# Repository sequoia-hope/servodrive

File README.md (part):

# servodrive

A round, motor-mounted servodrive: two Ø65 mm boards stacked on the back of a
brushless motor, with a magnetic rotary encoder on the shaft axis.

**Status: board A captured, placed and routed. 136 parts, 87 nets,
425 pin connections, every one of them made. DRC- and ERC-clean, and
KiCad's own extracted netlist matches the intended one connection for
connection. Re-routed 2026-09-22 with four of the simulation's changes
([below](#the-2026-09-22-changes)); board B is still an outline.
Board S, the single-board variant, captured, placed and routed 2026-09-23
from the same generators, re-routed the same day with TI's buck parts, and
re-placed and re-routed 2026-09-24 with an XT30 for the bus
([below](#board-s-one-board)).**

- **[spec.html](spec.html)** — the specification
- **[index.html](index.html)** — status, decisions, open questions; board A in the viewer (PCB and 3D tabs)
- **[single.html](single.html)** — board S, the single-board variant: captured, placed and routed, with the same viewer (SCH, PCB and 3D)

The pages are styled after Altium 365's workspace: a dark frame with the
project tree on the left, built by `shell.js` from each page's own headings.
The board viewer on the two board pages is
[pcbview](https://github.com/sequoia-hope/pcbview)'s (which began as this
project's own; `tools/regen.py` runs it from `~/Software/pcbview`):
`pcbview.toml` says what it shows, and `python3 tools/regen.py --board a|s`
builds it into `viewer/` and writes it into the page between
`<!-- pcbview:begin -->` and `<!-- pcbview:end -->`.
`viewer/a.html` and `viewer/s.html` are the same viewers filling the window.

Online at <https://sequoia-hope.github.io/servodrive/> (GitHub Pages, from
the root of `main`: the pages are plain files with relative links, and
`.nojekyll` keeps them that way). Served locally: `proj up servodrive`, then
`proj url servodrive` for the address.

## What it is

| | |
|---|---|
| Form | Two Ø65 mm round boards. The motor board bolts to the encoder's 4 × M3 pattern; the power/IO board to six perimeter M2.5. |
| Sections | Three 60° phase cells **adjacent**, 0–180°, then three 60° wedges. The CPU sits in the middle wedge, as far from the switching as a round board allows. |
| Encoder | MT6701 on the shaft axis, SSI to the CPU on the same board. No cable, no line drivers, no encoder port. |
| Bus | 60 V nominal, **12 V minimum**, 80 V silicon, TVS breakdown 71–79 V; XT30 |
| Phase current | **20 A RMS per phase, in bursts** — normal running is well below it, and no fins are planned (§4) |
| CPU | RP2350A, QFN-60 |
| Sensing | Two inline 1.0 mΩ shunts (2 × 2 mΩ) + **INA241A3** at 50 V/V = 50 mV/A, third phase reconstructed; bus voltage; FET temperature |
| Gate drive | EG2103 on a 12 V rail (LCSC C480654, 2,225 in stock, MOQ 5, $0.19) — interlock + 560 ns dead time |
| I/O | USB-C with full PD — a 20 V contract feeds VMOT; full-duplex RS-485 on two chained ports |

## The design point is 20 A RMS, and that word matters

Draft 0.2 used "20 A" for two different quantities: the thermal budget quoted
20 A **RMS per phase**, and the sense chain quoted ±20.6 A **instantaneous**.
Those differ by √2, so the sense chain clipped at 14.6 A RMS — it could not have
closed a current loop at the design point. One number now, and everything is
sized against it:

| | |
|---|---|
| Design point | 20 A RMS per phase — a burst figure since 2026-09-22, not a continuous rating |
| Peak the chain must see | 28.3 A |
| Sense full scale | ±29.0 A, worst-case output swing — 2.5% over the peak, see below |
| Board A dissipation | 10.7 W |
| Heatsink it would need to be continuous | ≤ 6.7 K/W, ≥ 100 cm² of external surface — not built |

## Current sensing

Full scale is set by the shunt. Keep this table, the schematic and the firmware
`SHUNT_RESISTOR` define pointed at each other — the sister project's F-14 is
exactly this drifting apart.

| Shunt (per sensed phase) | Gain | V/A | Measurable range |
|---|---|---|---|
| 1.0 mΩ (2 × 2 mΩ 2010) | 50 V/V | 0.050 | ±29.0 A |
| 2 mΩ (one desoldered) | 50 V/V | 0.100 | ±14.5 A |

Phase C is reconstructed as `Ic = -(Ia + Ib)`. Its two shunt footprints are
fitted with 0 Ω links so all three phases have the same series resistance.

Full scale is against the datasheet's **worst-case** output swing, V<sub>S</sub> − 0.2 V,
not the 0.07 V typical — that is what makes ±29.0 A rather than ±32 A, and it is
the number the design point has to clear. It does, by 2.5%.

**This took three goes.** Draft 0.2's 1.6 mΩ gave 80 mV/A to match the sister
project's firmware scaling, and ±20.6 A of full scale against a 28.3 A peak: it
would have clipped on every cycle above 14.6 A RMS. The first correction, 1.0 mΩ,
used the typical swing figure and had 2.5% of margin, which is not margin. 0.8 mΩ
(2 × 1.6 mΩ) survived the datasheet, and its precision mode landed on the sister
project's 80 mV/A. Then sourcing (2026-09-24) found no 1.6 mΩ 2010 at LCSC or
JLCPCB — 1 and 2 mΩ, nothing between — and the pair became 2 × 2 mΩ: back at
1.0 mΩ and its 2.5%, taken knowingly. The stocked alternative, 2 × 1 mΩ, reads
±58 A at 25 mV/A. Neither mode reproduces the sister project's 80 mV/A now, so
its firmware constants do not carry across.

**And the part number changed.** The 50 V/V grade of INA241 is **A3**, not A2.
INA240 numbers its gains A1 = 20, A2 = 50; INA241 numbers them A1 = 10, A2 = 20,
A3 = 50. Draft 0.2 carried the INA240 mapping across and specified a 20 V/V part
for a 50 V/V job.

## Relationship to rp2350-motor-controller

The sister project at `~/pcb/rp2350-motor-controller` supplies the MT6701
encoder circuit and its mount pattern (`hardware/encoder`), the power-stage part
choices, and a findings register that this board inherits the conclusions of
without inheriting the bugs. §9 of the spec lists which finding produced which
decision here.

Three things worth handing back:

- **F-17 is right, and draft 0.2 of this spec was wrong to doubt it — but not
  for the reason their register gives.** Their E-stop does brake. It brakes
  because `R1`, `R2`, `R21` and `R22` are 10 k pull-downs on both EG3113 inputs,
  and EG3113's LIN is active-low: a pulled-down LIN turns the low-side FET on.
  The driver on its own would coast. The consequence is worth knowing: their
  bridge **hard-shorts the motor at every reset and every power-up**, before
  firmware runs, with no current limit. On a spinning motor that is a braking
  current set only by winding resistance.
- **NCP5183DR2G** is a candidate answer to **F-40** (EG3113 unbuyable, currently
  blocking their orders): SOIC-8, 600 V, 4.3 A source/sink, matched 120 ns
  propagation delays, 50 V/ns dV/dt immunity, AEC-Q100, $0.92 at MOQ 1 with 2,883
  in stock. It gives up EG3113's interlock and dead time, which their own GaN
  evaluation argues they do not lean on. Also worth knowing: **EG2131 and FD2103S,
  the two obvious like-for-like swaps, are both out of stock.**
- **RP2350 erratum E9 reaches the gate driver.** A Bank 0 GPIO can latch around
  2.1–2.2 V, and at reset the pin is an input with a pull-down. Against EG Micro's
  internal 200 k pull-up on LIN that lands the driver input between V<sub>IL</sub>
  and V<sub>IH</sub>. Their pull-downs happen to defeat it; anyone copying the
  circuit without them should size an external pull deliberately.

## The channel interior to the screws

A phase cell is short of **angle**, not of area, and angle costs radius: a
millimetre of arc at R 20 is 2.9°, the same millimetre at R 29.5 is 1.9°. The
cell was 70° wide because small parts sat at small radius — a 1 µF 0805 beside
the gate driver was eating 30° on its own, while both MOSFETs together needed
only 18°.

The six boss pads sit on R 26.9–32.2, and **between them that band is empty**:
the heatsink land owns it on the outward face, and on the motor-facing face
nothing but the lead pads wants it. In the utility wedges that is still true and
the channel is still used. In a **phase** cell it turned out not to be — see
below — and only the clamp diode is left there, beside its own lead pad.

| | 70° cells | everything in the channel | **now** |
|---|---|---|---|
| Phase cell | 70° | 60° | **68°** |
| Utility wedge | 50° | 60° | **52°** |
| Bolt spacing | 70/70/70/50/50/50° | 60°, even | **68/68/68/52/52/52°** |
| In the channel, per cell | — | 6 parts | **1** — the clamp diode |
| Heatsink land | 286 mm² | 250 mm² | **279 mm²** |

**Routing took most of that back, and it was right to.** The middle column is
what the channel bought: 60° cells and an even bolt circle. What it cost only
showed up when the board was routed — a part in the channel can only be
connected if its nets are GND or the phase output, because the phase-output
pour owns B.Cu from R 25.9 to 28.9 beneath it, the heatsink land owns F.Cu from
R 29.2 above it, and the six boss pads cut the outer ring into six arcs. What
is left is a via corridor about 0.7 mm wide, twice per cell. Neither pour can
give the room back: the phase band is already 95 A/mm² at 3.0 mm and cannot
grow inward past R 25.6 without meeting the switch-node band.

So five of the six went back into the cell — the DC-link 100 n pair into the
DC-link row *ahead* of the bulk, where a high-frequency capacitor belongs; the
bootstrap diode beside the capacitor it charges; both input pulls onto the
driver's logic side with the VCC 100 n. Only the clamp diode stays, and its
nets are exactly GND and the phase output.

The cells had to pay for them: 67° is the floor, below which the DC-link row
runs into the perimeter boss, and 68° is what is set. That costs the even bolt
circle — the thing the 60° arrangement was pleasing for. It buys back
**29 mm² of heatsink land**, because the land's half-span is measured from the
cell edge.

Three consolidations paid for it: the per-driver 1 µF VCC bulk became one 4.7 µF
at the power link (three of them on one 0.1 A rail was two too many), the lead
pad narrowed from ±8.5° to ±7° (23 mm², still ample for a 14 AWG lead), and
`Row` learned to dodge parts in *other* rows — two rows that overlap radially
and sit at different angles can collide, and a packer that only looks at its own
row walks straight into them.

## The layout, second pass

The first routed board made 69 of 170 connections, and the diagnosis at
the time blamed the driver ring. Measuring the result said otherwise:
nearly every unrouted connection ended at the RP2350. In3, the only signal
layer that crosses the board, was almost empty, because nothing could get
out of the QFN to reach it. Three things were true of that board and are
not of this one.

**The QFN had no room to fan out.** A 0.4 mm pitch, 0.2 mm-wide pads, and a
via that is 0.46 mm across with 0.15 mm around it: a via per pin does not
fit in place, and it does not fit in two rows either. With 0.15 mm stubs it
takes four staggered rows, 2.9 mm deep, on every side — and the chip sat
0.3 mm from the parts either side of it, 0.8 mm from the row beyond it,
with its decoupling on the back directly under the pins where the vias had
to land. The CPU wedge is rebuilt around a clear band: the chip at R 21.15,
nothing within 2.9 mm of its pads on the front except the regulator
cluster (below), the six IOVDD 100 n on the back in two columns beside it,
the crystal in a row at R 29.9, and the flash turned so both its pad rows
face somewhere a via can go, with its own 100 n and the BOOTSEL resistor on
the back directly beneath its body. The signal header moved in to R 25.15,
where all twenty of its signal pads can take an escape via on the side away
from the edge.

**The FET gate pads faced the wrong way.** The gate is at one end of the
TDSON-8's source-pad row, and with the row pointing outward the gate sat at
R 27.9, walled in by the switch-node pour on three sides and the heatsink
land on the fourth. Both FETs are turned 180°, which swaps their sides, and
the gate pads are at R 24.4 facing the driver row across an empty 1.5 mm.
The gate resistors and input pulls are 0402s lying tangentially, so HO and
LO reach a pad at their own radius and the far pad points at the gate; the
bootstrap cap is a 0603 with its SW pad over the switch-node pour, so it
takes a via.

**The sense row on the back is arranged for arcs, not for a router.** The
amplifier is at the cell's centre with its SNSP pin, the switch-node-side
tap and the filter cap all clockwise of it within 0.4 mm of R 18.4, so
that SNSP is one arc between the amplifier's pad rows with a spur down to
each pad, and SNSN is a second arc beside it to the filter cap, a via at
the amplifier and a via in the tap at the shunt, and one run on In3
between them. The gate bleeds moved from that row to directly beneath the
gate resistors: the high side's radial under its resistor, the low side's
further out under the gate's own radial track, each with one via through
both pads. The NTC moved inside the row where its pad can take a via. The
flash is turned so that each pad row's radial order is the chip's QSPI pin
order along its side and the In3 runs between them do not cross.

**Every 20 A pad takes a via, and the router never sees those nets.** The
shunts moved from either side of the cell to side by side under the
switch-node island, between the two FETs' via clusters — nowhere else on
the back is clear of the DC-link caps' vias coming through from the other
face — with the SW pads over the switch-node pour and the PHASE pads in the
phase-output pour, the lead pad directly beyond. The sense taps sit beside
them, the clamp in the channel beside the lead pad where the pour reaches
out to it. The switch-node pour on B.Cu comes in to R 20 so the driver's VS
pin, the bootstrap cap, the bleed and the tap all stitch. +3V3 is a plane on
In2 that is now the whole centre disc as well as the CPU wedge, so each
cell's sense amplifier taps it with a stub. With all of that
stitched, `tools/deadcheck.py` proves it and `route.py` takes VBUS, the
switch nodes, the phase outputs and +3V3 away from the router: pours become
keepouts, pads lose their net and get a halo the width of their clearance
class. It cost the cells 0.9 mm of FET spacing, a 1206 DC-link bulk cap
instead of a 1210 (the 1210 ran into the perimeter boss), and a SOD-323
bootstrap diode.

### The RP2350, from the reference design

The chip's regulator and decoupling are Raspberry Pi's, copied from the
RP2350A minimal design (RP-006440) in the chip's own frame to the 0.05 mm:
the 3.3 µH 2016 inductor 3.8 mm from VREG_LX with the VIN, DVDD and AVDD
4.7 µF stacked beside it, the two by the inductor on the reference's own
small-pad 0402 footprint because the switch node's neck passes between
their pads; 33 Ω into VREG_AVDD; 27 Ω in series with each USB line; five
small pours around the regulator pins; a ring of 1V1 copper under the chip
joining the four DVDD pins, which the fan-out tool reaches with a stub from
each; and the reference's own two F.Cu tracks, VREG_AVDD out to its RC and
DVDD pin 50 out to the regulator's output pour (the second is only laid if
the fan-out beside it leaves the room, and here it does not, so the ring
and the output pour meet through a via each and a run on In3 that the
fan-out tool lays itself, dodging the via field). Two of the pours turned
out not to fill under the 0.15 mm clearance this board runs — between two
0.4 mm-pitch pads a pour is 0.3 mm wide and breaks at their corners — so
VREG_LX gets a 0.15 mm track as well, threaded between the VIN capacitor's
pads the way the reference's pour is.

Three things capture found while doing it, all in the netlist rather than
the layout:

- **The bootstrap diode was backwards.** `Device:D` numbers its pins
  1 = cathode, 2 = anode, and so does the footprint; the netlist had the
  cathode on +12V. A bootstrap diode charges the cap *from* the rail.
- **VREG_AVDD was tied straight to +3V3.** The reference feeds it through
  33 Ω with its own 4.7 µF.
- **USB had no series resistors.** 27 Ω each, as the reference.

The crystal's load caps stay at 27 p where the reference uses 15 p: the
reference's crystal is a different part with a different CL, and the value
is the crystal's to decide.

## Layout

```
tools/sexp.py        a reader/writer for KiCad's s-expressions
tools/geometry.py    every dimension and every derived number; regenerates img/*.svg
tools/placement.py   the board-A floorplan, and the checks that keep it legal
tools/placement_s.py board S, the single-board variant: its floorplan (layout()),
                     drawn to img/board_s_*.svg and single.html's tables
tools/placement_e.py board E, the Ethernet daughter board: a placement sketch
                     over board S as routed, drawn to img/board_e_plan.svg
tools/schematic.py   the board-A netlist, and the sheets it emits
tools/schematic_s.py board S's netlist, built from schematic.py's own functions
tools/gen_boards.py  emits the KiCad projects from the three above; --board s
                     emits board S alone
tools/stitch.py      puts a via in every pad that sits over its own plane
tools/fanout.py      the copper the router could not make: the RP2350's escape
                     vias, the gate and sense arcs, the escapes, the plane taps
tools/deadcheck.py   proves every pad on a net route.py demotes already
                     touches copper of its own net
tools/padpos.py      pad centres of a placed Part, polar, without a board
tools/finish.py      a maze router over the board's free space, for whatever
                     freerouting gives back still in pieces
tools/route.py       hands the rest to freerouting, headless, and brings it back
tools/regen.py       remakes what the pages show after gen_boards.py or
                     route.py (both run it): the board viewer (pcbview build),
                     board S's build status, board S's simulation
pcbview.toml         the board viewer: which boards and pages, the sheet names,
                     the layer notes, the stand-in 3D models, the LCSC table
hardware/
  parts/3dmodels/    two STEP models the footprints name and KiCad's library
                     lacks, and one it has but kicad-cli cannot mesh, flattened;
                     stand-ins for the 3D viewer, mapped in pcbview.toml
                     (sources in its README)
  parts/lcsc.csv     the LCSC numbers chosen so far, by value and footprint, for
                     the 3D viewer's part pane; a part not in it has none yet
  parts/             two symbols copied in, three DERIVED (EG2103, INA241A3,
                     W25Q16JV; board S's SIT3088, SIT65HVD75 and W25Q80DV too), two copied from the RP2350A reference design
                     (the 2016 inductor, a small-pad 0402) and five GENERATED
                     footprints (the FET with 16 thermal vias for the low side
                     and 20 for the high, heatsink boss, heatsink land, phase pad)
  motor_board/       servodrive_A — 6 layer, 2 oz outer, 136 parts, 87 nets
  power_board/       servodrive_B — 4 layer, 2 oz outer, outline only
  single_board/      servodrive_S — board S, 6 layer, board A plus board B's minimum
img/                 generated drawings — do not edit by hand
viewer/              built by pcbview — do not edit by hand: a/ and s/ (sch/,
                     layers/, 3d/ with board.glb and parts.json), assets/ (its
                     scripts, viewer.css, three.js), a.html and s.html
shell.js             the frame every page shares, after Altium 365: top bar, the
                     PROJECT tree read off each page's headings, the sheet bar
style.css            the one stylesheet, A365's palette (sim/report uses it too);
                     the viewer's own is viewer/assets/viewer.css
vendor/fonts/        Inter, latin and greek (OFL)
spec.html            the specification
index.html           project status
```

The three tools are checked against each other before anything is written:
`gen_boards.py` will not emit a board if the floorplan overlaps itself, or if
any part is on the board and not in the netlist, or in the netlist and not on
the board, or if their footprints disagree, or if a symbol pin has no net.

Run `python3 tools/geometry.py` after changing any dimension, then
`python3 tools/gen_boards.py --force` to re-emit the boards. `gen_boards.py`
refuses to run at all if `placement.py`'s checks fail, so a board that overlaps
itself cannot be written.

`--force` rewrites the boards from scratch, which now means **throwing away the
routing**. Without it `gen_boards.py` keeps the existing `.kicad_pcb` and only
re-renders. `--force` also runs the stitcher and the fan-out, so the board it
writes is already half made; after it, re-run `python3 tools/route.py --rounds 4
--loose` for the rest. The moment you move a part or a track in KiCad by hand,
stop using `--force` at all.

## Hardware

Both projects are KiCad 9, DRC- and ERC-clean. Board origin is the shaft axis on
both, so the stack aligns.

| | Board A | Board B |
|---|---|---|
| Stackup | 6 layer, 2 oz outer / 1 oz inner | 4 layer, 2 oz outer |
| Diameter | Ø65 mm | Ø65 mm |
| Motor mount | 4 × M3 at (±12.5, 0), (0, ±9.5) | — |
| Stack mount | 6 × M2.5 at R = 29.5 | 6 × M2.5 at R = 29.5 |
| Placed | 136 parts, 78 front / 58 back, 10 DNP | — |
| Captured | 136 components, 87 nets, 425 connections | — |
| Routed | 1361 track segments, 278 vias, all 425 connections, **DRC clean** | — |

The F.Cu → In1 prepreg is **0.1 mm**, and that is a load-bearing number, not a
stackup detail: it is what puts the ground plane under the commutation loop and
holds loop inductance at 0.39 nH of PCB, 2.0 nH all in, 1.7 V of overshoot on
80 V silicon.

Design rules: 0.15 mm track and clearance everywhere except the 60 V nets, which
get 0.4 mm; vias 0.5/0.20 signal, 0.6/0.30 power, 0.8/0.40 phase; **0.5 mm
hole-to-hole**. That last one is deliberate — JLCPCB fills and copper-caps
via-in-pad for free on 6-layer boards, which is what lets the pad centres be
holes at all, but it wants 0.5 mm between them, and the sister project's F-48 is
the cost of discovering that after 253 via pairs were already too close.

Two of those numbers moved during routing, and both were wrong before:

- **0.15 mm, not 0.20, on the power and analog classes.** A 0.65 mm-pitch
  VSSOP-8 has 0.15 mm between adjacent pins, so a 0.20 mm class made every
  INA241 a clearance violation that no layout could fix. 0.15 is also JLCPCB's
  floor for 2 oz outer copper, so nothing is given up.
- **0.20 mm drills on the 0.5 mm vias, not 0.25.** The annular ring is
  (diameter − drill) / 2, so 0.25 left 0.125 mm against this project's own
  0.13 mm minimum. The default via was illegal under the default rules, and
  nothing noticed until there were vias on the board to check.

Verify after any change:

```sh
python3 tools/placement.py       # floorplan: overlaps, bounds, cross-layer
python3 tools/schematic.py       # netlist, and that it matches the placement
python3 tools/deadcheck.py hardware/motor_board/servodrive_A.kicad_pcb
python3 tools/route.py --rounds 4 --loose   # route headless, import, finish, DRC
cd hardware
kicad-cli pcb drc motor_board/servodrive_A.kicad_pcb
kicad-cli sch erc motor_board/servodrive_A.kicad_sch
kicad-cli sch export netlist --format kicadsexpr -o /tmp/n.net \
    motor_board/servodrive_A.kicad_sch     # then diff it against schematic.nets()
```

That last one is the check worth keeping: KiCad's own extracted netlist against
the one this repo intended, net by net and connection by connection. It is how
the sub-symbol naming bug below was caught, and it is the only thing that proves
the labels actually connect what they look like they connect.

## Routing

Most of board A is not routed and never will be. GND is two solid inner
planes, VBUS is a sector of a third, +3V3 is the rest of that third — the
CPU wedge and the whole centre disc — and each switch node and phase output
is a pour on F.Cu and B.Cu, because 20 A does not go down a track and
IPC-2152 wants about 6 mm of 2 oz copper for it. What is left is the
signals, and those go to freerouting — less the ones it turned out to do
badly, which are made first, as copper, and taken away from it.

Five tools do the rest, and freerouting is the fourth of them rather than
the whole story. They all run from `gen_boards.py` and `route.py`, so the
board is still reproducible from `geometry.py`:

- `tools/stitch.py` puts a via in every pad that sits over a plane or pour
  of its own net. 104 of them.
- `tools/fanout.py` makes the connections the router could not. It escapes
  the RP2350: a 0.15 mm stub from the centre of every one of its sixty
  pads and a via at the end of it, in planned staggered rows, the stub
  threaded through the rows in front of it. It joins the four DVDD pins to
  the 1V1 ring under the chip. It wires each FET's gate to its gate
  resistor — radially in from the gate, an arc along the band between the
  driver row and the FETs, radially in to the resistor's pad — and puts a
  via through that pad into the gate bleed's pad directly beneath it, so
  the whole gate net is copper. It wires SNSP and half of SNSN as arcs
  between the sense amplifier's two pad rows on the back, and joins SNSN's
  other half on In3. It gives the flash, the signal header and the
  amplifiers' remaining pads a stub and a via each. And it taps every pad
  on a plane net that is not over its plane — +3V3 mostly, and the few
  ground pads a via would not fit in — with a stub to a via that is.
- `tools/deadcheck.py` then proves that every pad on VBUS, the three switch
  nodes, the three phase outputs and +3V3 already touches copper of its own
  net.
- `route.py` hands what is left to freerouting: it takes the demoted nets
  and every net already finished away from the router entirely — their
  pours become keepouts, their In2 planes go, their pads lose the net and
  get a keepout halo the width of their clearance class.
- `tools/finish.py` is a maze router, and it goes last, on what the router
  gives back still in pieces — deterministically, at 45 degrees, every
  segment checked against the same clearance test the fan-out uses, and
  allowed to move the router's own wires to do it.

Every track and via the tools make is **locked**. That is not a courtesy
to the KiCad user: it is how `route.py` tells the tools' copper from the
router's on the way out and on the way back, below.

### The maze

The last few connections are not hard because the board is full. They are
hard because they are *last*: the lanes out of the QFN's via field are
spent on whichever nets reached them first, and the ones left over cannot
be routed by anything that will not move what is already there.
`tools/finish.py` is that: a maze router that knows the whole board, and
rips up when it has to.

It rasterises. One bitmap per routable layer —
F.Cu, In3 and B.Cu; In1 and In4 are ground and In2 is the power planes — at
0.05 mm, every foreign shape drawn as it is and then grown by the clearance
it wants, 0.15 mm or 0.4 for the 60 V nets, by a distance transform. Then
A\* from one piece of the net to the other, eight-connected so that every
step is 45 degrees, with a via as a move between layers wherever a via
would fit. The path that comes back is a chain of cells, which is not what
anyone wants on a board, so it is folded back into as few segments as the
free space allows: from each point, the farthest point it can be joined to
by one straight run and one diagonal.

Two things it has to know that KiCad's clearance rules do not cover, and
both were found by DRC after the first run:

- **The board edge.** The clearance test is between copper and copper; the
  outline is neither. The maze knew the edge and the simplifier did not, so
  it cut a corner 0.4 mm outside the board — twice, on two layers. The
  simplified path answers to the grid as well as to the clearance test now.
  (And the edge radius comes from the outline circle rather than from the
  board's bounding box, which is bigger by half the outline's 0.1 mm
  stroke.)
- **A bare drill.** An M3 mounting hole is NPTH: it has no copper, so no
  copper clearance rule mentions it, and `min_hole_clearance` is the only
  thing keeping a track off it. Seven tracks ran within 0.16 mm of the four
  mounting holes before the grid was told about drills.

The grid is a rasterisation, so it is conservative by 0.03 mm — a little
over half a cell, which is what a drawn boundary is worth. What it proposes
is still checked exactly, segment by segment; what the exact test rejects
is punched out of the grid and the route planned again. In practice one
step in seven hundred comes back, short by a micron, and the detour costs
nothing.

When a net cannot be made at all, the maze rips up: every unlocked track
near the gap — the router's copper, never the tools' — comes out by whole
nets rather than by the segments that happen to fall in the box, the
connection is made, and then the nets that were displaced are made again,
longest first, each of them allowed to rip up in turn. If any of them
cannot be, the whole attempt is undone and the box grows.

**Undoing it is the part that was wrong.** The first version recorded which
items were on the board and which had been taken off, and undid an attempt
by deleting everything that had appeared since and putting the recorded
ones back. That is correct until an attempt rips up inside an attempt: the
inner one puts its copper back as *new* items, the outer one then deletes
them as things that were not there before, and they are in nobody's
record. The log said four connections made; KiCad said forty-one
unconnected. The undo copies the whole board now, and there is a guard
around the whole pass: KiCad's own count of what is unconnected, before
and after, and if the maze has not improved it the pass is thrown away and
the board stands as the router left it.

**Order matters more than either router.** Given the whole board first,
with only the fan-out's copper in the way, the maze makes 49 of the 61
nets and leaves 12 — and freerouting, handed a board full of locked
copper, then closes one. Given what freerouting leaves, six connections,
it makes four. Seeding it with those six by name and running it first came
back with nine. It does not matter which nets get the lanes out of the via
field; it matters how many lanes there are.

### Why the fan-out is a tool and not a pass

A 0.4 mm-pitch QFN cannot take a via per pin in place. The pads are 0.2 mm
wide with 0.2 mm between them, a via is 0.46 mm across and wants 0.15 mm
around it, and every via row that goes in front of the chip takes lane
width from the stubs that still have to pass it. The arithmetic: with
0.15 mm stubs, a row of vias every fourth pin leaves 0.84 mm between two of
them, and the three stubs that pass through need 0.75. That is the whole
margin, 0.09 mm, and it is why the fan-out is four rows deep.

It is also why the stubs are threaded rather than bent. A stub passing a
neighbour's via steps 0.06 mm aside for the length of that via and comes
back; held aside across a whole row-to-row interval, two neighbours passing
vias on opposite sides of themselves met in the middle, 0.03 mm too close.
The search is a small dynamic programme over (waypoint, lateral offset)
that strays from the pad's axis as little as it can, and it finds 51 of the
52 vias in about five seconds.

### The via in the pad

For every SMD pad whose net has a filled zone on some other layer directly
beneath it, the stitcher puts a via in the pad. That is via-in-pad, which
JLCPCB fills and plates over for free on six layers — which is the only
reason a pad centre is allowed to be a hole. It places 104 and
leaves 146 connections to the fan-out and the router.

It is worth doing by hand because the router does it badly. Given the board
whole, freerouting queued all 112 ground pads as isolated, threw the vias
away and ran 0.2 mm traces across the top and bottom layers instead — 92 of
the 177 connections it could not finish on the first board were this.

Two rules matter and the first version of the stitcher got the second wrong:

- the via's pad has to fit inside the SMD pad, and its hole has to keep
  `min_hole_clearance` from foreign copper;
- **the via's pad has to clear foreign copper on every layer, not just the
  pad's.** A through via's annulus exists on all six. Fitting inside an F.Cu
  pad says nothing about what the same copper does on B.Cu, and checking
  only the drill put 33 clearance violations on the board.

### What the round trip got to decide

Everything below was found by measuring the result, not by reading about it.

- **Freerouting does not treat a Specctra `plane` as connecting anything.** So
  ground is taken off the table before export: the planes go, the net goes, and
  In1/In4 are declared `power` layers, which is Specctra's way of saying *not
  for routing*. The pads stay, as obstacles with no net, which is exactly what
  they are to a router that is not routing them.
- **A `plane` is not an obstacle either.** `ignore_conduction` defaults to
  true, so given the 20 A pours as planes the router lays a foreign track
  straight through them and KiCad cuts the pour around it. Every pour is a
  keepout by the time the router sees it, and every pad on those nets is
  stitched to its pour first.
- **A protected via is protected on its pad's layer, by the pad, and nowhere
  else.** The ground vias are removed from the DSN and each leaves a
  keepout on the four signal layers, or the router runs a trace under the
  pad on In3 and the via lands on it when the stitch is restored.
- **KiCad's SES import takes a via's diameter from the Specctra padstack and
  its drill from the netclass.** Those are not the same thing. A stitching via
  in a pad too small for the 0.8/0.40 the Phase class wants is 0.46/0.20, and
  it came back 0.46/**0.40** — a 0.03 mm annular ring, fifteen of them. The
  diameter is the honest half of the pair, so `route.py` rebuilds every drill
  from it after import.

  The first attempt at this was to stop offering the 0.46 padstack in the DSN,
  and it made things worse in a way worth recording: freerouting then wrote a
  session that *used* that padstack for the pre-placed vias without *defining*
  it, and KiCad's importer rejected the whole file with no message at all.
- **Specctra has no hole-to-hole rule.** `via_via` and `via_pin` copper
  clearance stand in for it: 0.3 mm between two 0.5/0.20 vias puts their holes
  0.5 mm apart, which is the rule this board is built to. And a class with a
  rule of its own does not inherit them from the structure rule — measured
  as two vias on Analog-class nets 0.48 mm hole to hole — so every class
  rule carries both.
- **The router routes right up to the boundary it is given.** The outline is
  pre-inset by `min_copper_edge_clearance` before export; the board is a circle
  about the shaft axis, so the inset is exact.
- **`PAD::GetLayer()` answers F.Cu for a pad on a flipped footprint.** Only the
  layer set knows. Believing it put fifteen vias between a B.Cu pad and a B.Cu
  pour, which DRC reports as "connected on only one layer", and is.
- **KiCad's DRC report names items by uuid**, and a library footprint
  embedded verbatim carries the library's pad uuids, so six FETs shared
  them and the unconnected list named the wrong FET's gate for three runs.
  Every embedded item gets a uuid of its own now.

### What freerouting turned out to do

All of it measured, most of it by reading the router's log and some of it
by reading its bytecode, after four runs in a row stopped at the same
thirty connections.

- **A wire touches a pad only if it ends on the pad's centre, exactly.**
  `Trace.get_normal_contacts` compares the wire's end with
  `DrillItem.get_center()` using `equals`. Freerouting computes that centre
  itself, from the placement rotation, in doubles rounded to its 0.1 µm
  grid; KiCad writes wire coordinates to the whole micron. So a stub that
  started 0.05 mm inside its pad was a separate island to freerouting, and
  so was one that started on the pad's centre: it then queued 119
  connections between a pad and its own stub, could insert none of them,
  and spent every pass's ripup budget on them. `route.py` now rewrites
  every wire end within 30 µm of a pin or a via of its net to the centre
  freerouting will compute. The count of incompletes it starts from fell
  from 196 to KiCad's own.
- **In 45-degree mode it cannot leave a pad that is not on the grid.** Its
  search tree wraps a tilted pad in the pad's bounding octagon. On a round
  board every pad is tilted; for the FETs' 0.85 × 0.5 mm gate pads the
  octagon plus clearance runs into the halos beside them ("no accessible
  expansion doors", every gate, every pass), and for the flash's 0.5 mm
  pitch and the amplifiers' 0.65 it overlaps the neighbours. Free-angle
  mode is exact and routes them, and a pass of it took twenty-five minutes
  where a 45-degree pass takes five seconds — so those pads are not left
  to it.
- **A protected wire is a bad target.** The maze search reaches the stub
  before the via at its end, and a junction into a protected trace cannot
  be inserted ("the new connection could not be inserted", 791 times in
  one run); a three-segment protected polyline joined twice sends
  normalization round a loop for ever (32,000 "max normalization depth"
  lines in forty seconds, in a board of four pads; the gate arcs did the
  same to the real board, pass 1 never finishing). So the router is not
  shown the stubs at all: a pin that has its stub and its via leaves its
  net's pin list, the stub becomes a keepout, and the net's end is the via —
  a circle, on the grid at any angle, nothing to tee into. A net with no
  pins left and two vias routes fine. The nets the fan-out finishes
  outright — the gates, bleed and all, SNSP, SNSN, the 1V1 link — are
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
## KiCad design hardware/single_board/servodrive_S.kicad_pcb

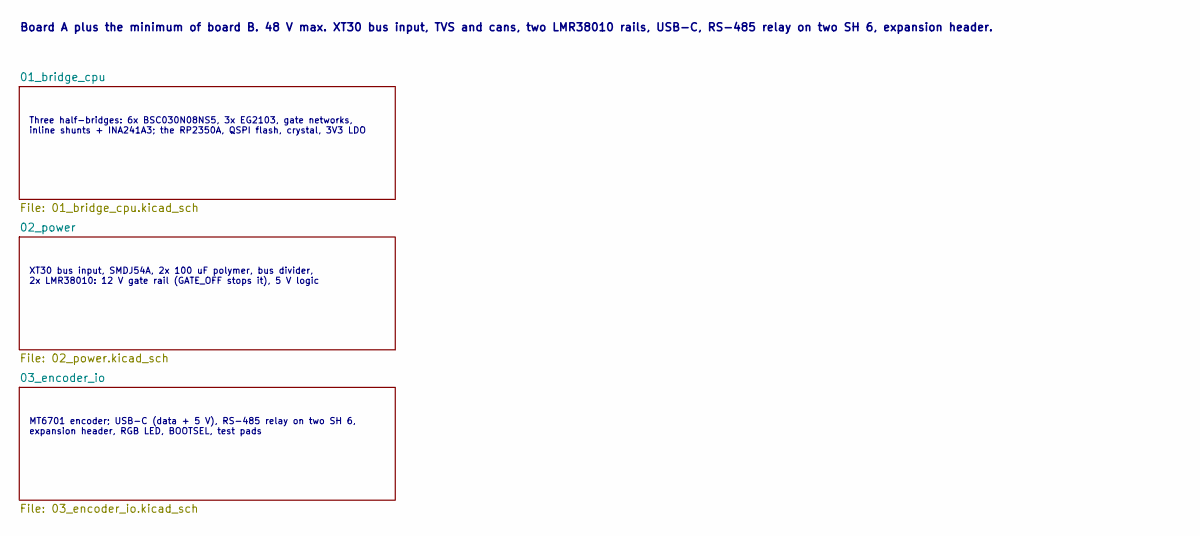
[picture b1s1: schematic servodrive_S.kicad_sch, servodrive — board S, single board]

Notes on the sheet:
Three half-bridges: 6x BSC030N08NS5, 3x EG2103, gate networks, inline shunts + INA241A3; the RP2350A, QSPI flash, crystal, 3V3 LDO
XT30 bus input, SMDJ54A, 2x 100 uF polymer, bus divider, 2x LMR38010: 12 V gate rail (GATE_OFF stops it), 5 V logic
MT6701 encoder; USB-C (data + 5 V), RS-485 relay on two SH 6, expansion header, RGB LED, BOOTSEL, test pads
Board A plus the minimum of board B. 48 V max. XT30 bus input, TVS and cans, two LMR38010 rails, USB-C, RS-485 relay on two SH 6, expansion header.

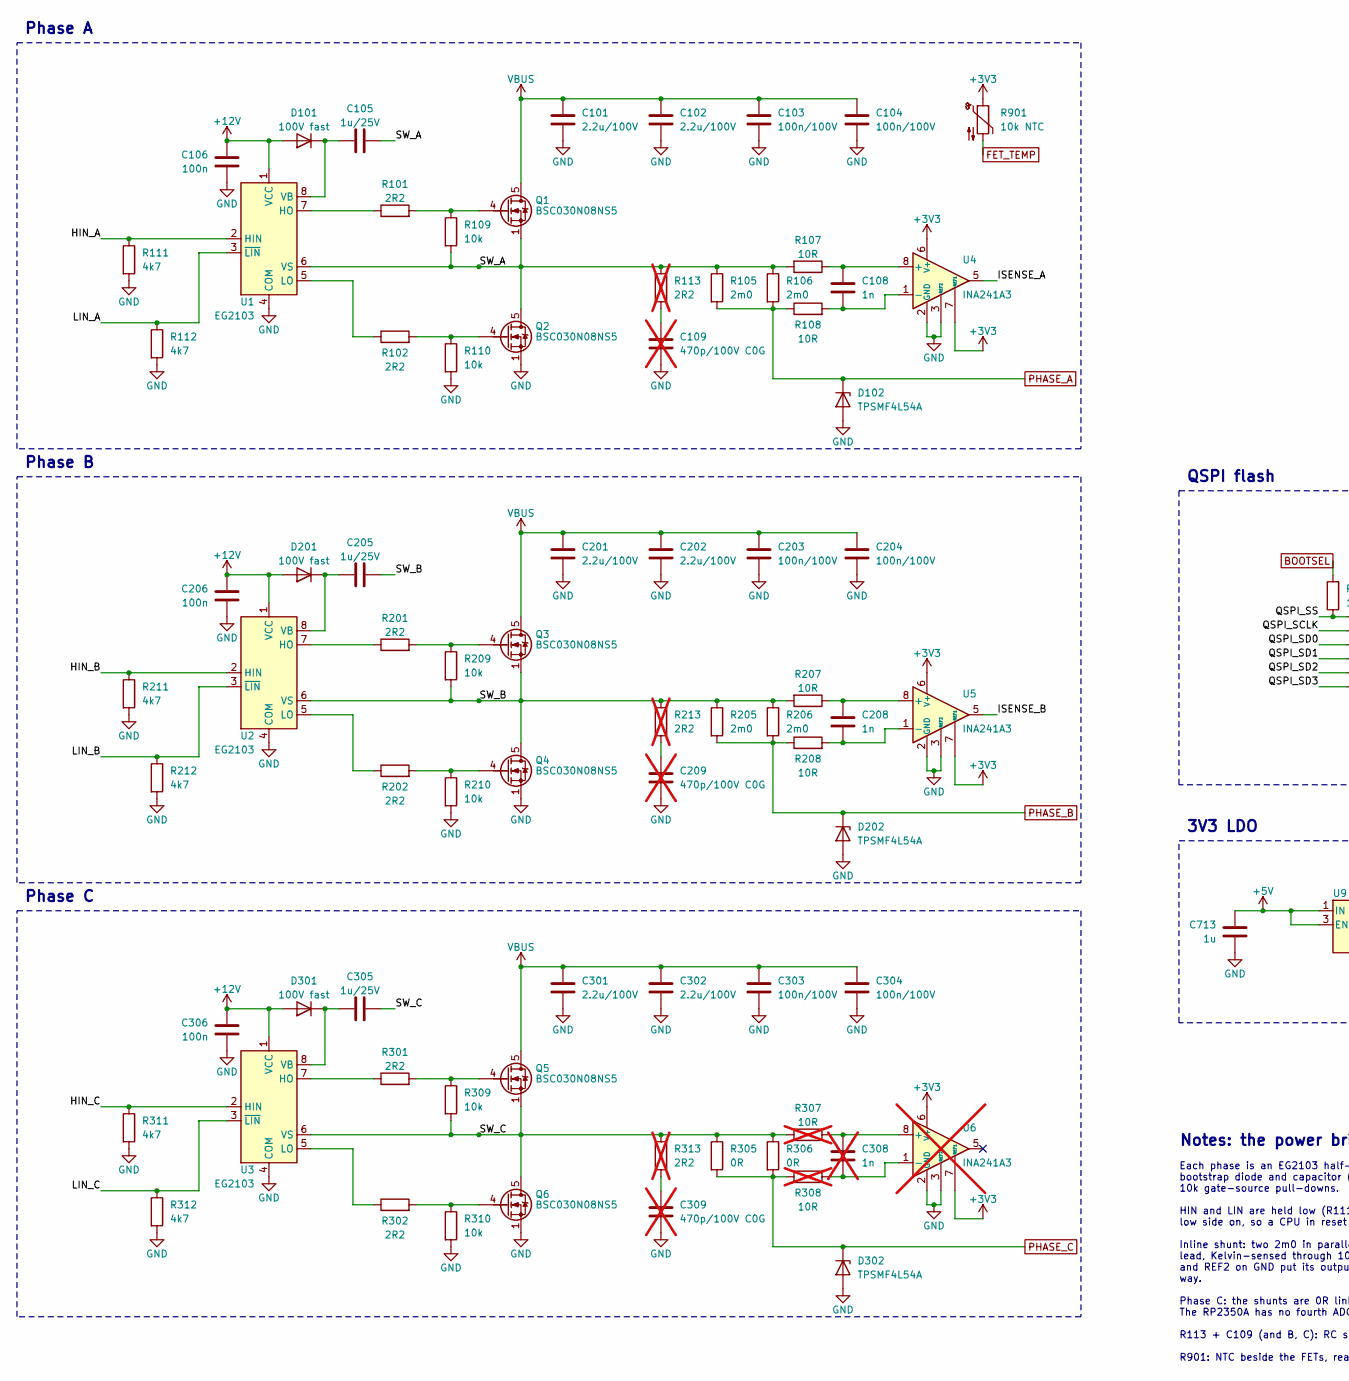
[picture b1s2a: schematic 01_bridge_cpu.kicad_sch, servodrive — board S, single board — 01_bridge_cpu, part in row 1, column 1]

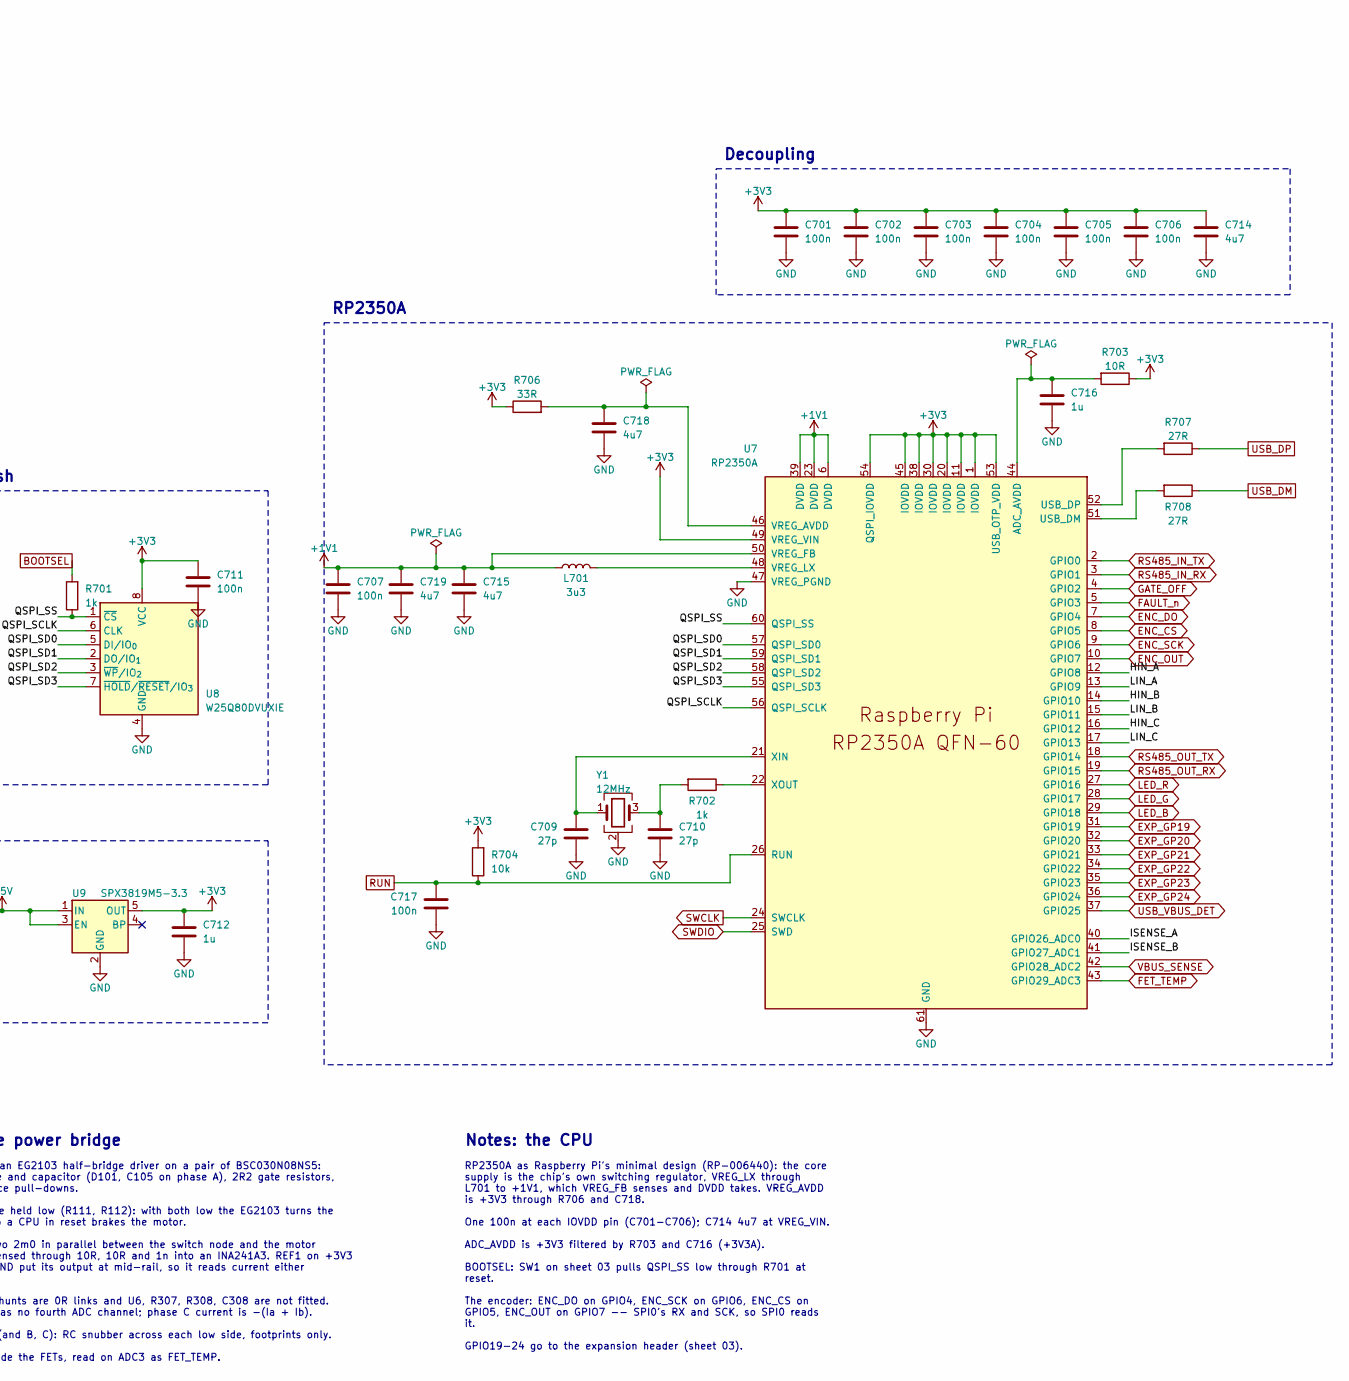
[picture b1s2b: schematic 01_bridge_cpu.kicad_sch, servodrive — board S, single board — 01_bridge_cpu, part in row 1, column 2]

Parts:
C101, C102, C201, C202, C301, C302: 2.2u/100V; C_1206_3216Metric
C103, C104, C203, C204, C303, C304: 100n/100V; C_0603_1608Metric
C105, C205, C305: 1u/25V; C_0603_1608Metric
C106, C206, C306: 100n; C_0603_1608Metric
C108, C208: 1n; C_0603_1608Metric
C109, C209, C309: 470p/100V C0G; C_0603_1608Metric; not fitted
C308: 1n; C_0603_1608Metric; not fitted
C701, C702, C703, C704, C705, C706, C707, C711, C717: 100n; C_0402_1005Metric
C709, C710: 27p; C_0402_1005Metric
C712, C713: 1u; C_0603_1608Metric
C714, C715: 4u7; C_0402_1005Metric_small_pads
C716: 1u; C_0402_1005Metric
C718, C719: 4u7; C_0402_1005Metric
D101, D201, D301: 100V fast; D_SOD-323
D102, D202, D302: TPSMF4L54A; D_SOD-123F
L701: 3u3; L_pol_2016
Q1, Q3, Q5: BSC030N08NS5; TDSON-8-1_ThermalVias_HS
Q2, Q4, Q6: BSC030N08NS5; TDSON-8-1_ThermalVias
R101, R102, R201, R202, R301, R302: 2R2; R_0402_1005Metric
R105, R106, R205, R206: 2m0; R_2010_5025Metric
R107, R108, R207, R208: 10R; R_0603_1608Metric
R109, R110, R209, R210, R309, R310: 10k; R_0603_1608Metric
R111, R112, R211, R212, R311, R312: 4k7; R_0402_1005Metric
R113, R213, R313: 2R2; R_0603_1608Metric; not fitted
R305, R306: 0R; R_2010_5025Metric
R307, R308: 10R; R_0603_1608Metric; not fitted
R701, R702: 1k; R_0402_1005Metric
R703: 10R; R_0402_1005Metric
R704: 10k; R_0402_1005Metric
R706: 33R; R_0402_1005Metric
R707, R708: 27R; R_0402_1005Metric
R901: 10k NTC; R_0603_1608Metric
U1, U2, U3: EG2103; SOIC-8_3.9x4.9mm_P1.27mm
U4, U5: INA241A3; TSOT-23-8
U6: INA241A3; TSOT-23-8; not fitted
U7: RP2350A; RP2350-QFN-60-1EP_7x7_P0.4mm_EP3.4x3.4mm_ThermalVias
U8: W25Q80DVUXIE; Winbond_USON-8-1EP_3x2mm_P0.5mm_EP0.2x1.6mm
U9: SPX3819M5-3.3; SOT-23-5
Y1: 12MHz; Crystal_SMD_2520-4Pin_2.5x2.0mm

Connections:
+1V1: C707.1, C715.1, C719.1, L701.1, U7.6 (DVDD), U7.23 (DVDD), U7.39 (DVDD), U7.50 (VREG_FB)
+3V3: C701.1, C702.1, C703.1, C704.1, C705.1, C706.1, C711.1, C712.1, C714.1, R703.1, R704.2, R706.1, R901.1, U4.6 (V+), U4.7 (REF1), U5.6 (V+), U5.7 (REF1), U6.6 (V+), U6.7 (REF1), U7.1 (IOVDD), U7.11 (IOVDD), U7.20 (IOVDD), U7.30 (IOVDD), U7.38 (IOVDD), U7.45 (IOVDD), U7.49 (VREG_VIN), U7.53 (USB_OTP_VDD), U7.54 (QSPI_IOVDD), U8.8 (VCC), U9.5 (OUT); also elsewhere on the board
+3V3A: C716.1, R703.2, U7.44 (ADC_AVDD)
+5V: C713.1, U9.1 (IN), U9.3 (EN); also elsewhere on the board
+12V: C106.1, C206.1, C306.1, D101.2 (A), D201.2 (A), D301.2 (A), U1.1 (VCC), U2.1 (VCC), U3.1 (VCC); also elsewhere on the board
BOOTSEL: R701.2; also elsewhere on the board
ENC_CS: U7.8 (GPIO5); also elsewhere on the board
ENC_DO: U7.7 (GPIO4); also elsewhere on the board
ENC_OUT: U7.10 (GPIO7); also elsewhere on the board
ENC_SCK: U7.9 (GPIO6); also elsewhere on the board
EXP_GP19: U7.31 (GPIO19); also elsewhere on the board
EXP_GP20: U7.32 (GPIO20); also elsewhere on the board
EXP_GP21: U7.33 (GPIO21); also elsewhere on the board
EXP_GP22: U7.34 (GPIO22); also elsewhere on the board
EXP_GP23: U7.35 (GPIO23); also elsewhere on the board
EXP_GP24: U7.36 (GPIO24); also elsewhere on the board
FAULT_n: U7.5 (GPIO3); also elsewhere on the board
FET_TEMP: R901.2, U7.43 (GPIO29_ADC3); also elsewhere on the board
GATE_OFF: U7.4 (GPIO2); also elsewhere on the board
GH_A: Q1.4 (G), R101.2, R109.1
GH_B: Q3.4 (G), R201.2, R209.1
GH_C: Q5.4 (G), R301.2, R309.1
GL_A: Q2.4 (G), R102.2, R110.1
GL_B: Q4.4 (G), R202.2, R210.1
GL_C: Q6.4 (G), R302.2, R310.1
GND: C101.2, C102.2, C103.2, C104.2, C106.2, C109.1, C201.2, C202.2, C203.2, C204.2, C206.2, C209.1, C301.2, C302.2, C303.2, C304.2, C306.2, C309.1, C701.2, C702.2, C703.2, C704.2, C705.2, C706.2, C707.2, C709.2, C710.2, C711.2, C712.2, C713.2, C714.2, C715.2, C716.2, C717.2, C718.2, C719.2, D102.2 (A), D202.2 (A), D302.2 (A), Q2.1 (S), Q2.2 (S), Q2.3 (S), Q4.1 (S), Q4.2 (S), Q4.3 (S), Q6.1 (S), Q6.2 (S), Q6.3 (S), R110.2, R111.2, R112.2, R210.2, R211.2, R212.2, R310.2, R311.2, R312.2, U1.4 (COM), U2.4 (COM), U3.4 (COM), U4.2 (GND), U4.3 (REF2), U4.4 (GND), U5.2 (GND), U5.3 (REF2), U5.4 (GND), U6.2 (GND), U6.3 (REF2), U6.4 (GND), U7.47 (VREG_PGND), U7.61 (GND), U8.4 (GND), U9.2 (GND), Y1.2 (G), Y1.4 (G); also elsewhere on the board
HIN_A: R111.1, U1.2 (HIN), U7.12 (GPIO8)
HIN_B: R211.1, U2.2 (HIN), U7.14 (GPIO10)
HIN_C: R311.1, U3.2 (HIN), U7.16 (GPIO12)
HO_A: R101.1, U1.7 (HO)
HO_B: R201.1, U2.7 (HO)
HO_C: R301.1, U3.7 (HO)
ISENSE_A: U4.5, U7.40 (GPIO26_ADC0)
ISENSE_B: U5.5, U7.41 (GPIO27_ADC1)
LED_B: U7.29 (GPIO18); also elsewhere on the board
LED_G: U7.28 (GPIO17); also elsewhere on the board
LED_R: U7.27 (GPIO16); also elsewhere on the board
LIN_A: R112.1, U1.3 (~LIN), U7.13 (GPIO9)
LIN_B: R212.1, U2.3 (~LIN), U7.15 (GPIO11)
LIN_C: R312.1, U3.3 (~LIN), U7.17 (GPIO13)
LO_A: R102.1, U1.5 (LO)
LO_B: R202.1, U2.5 (LO)
LO_C: R302.1, U3.5 (LO)
PHASE_A: D102.1 (K), R105.2, R106.2, R108.1; also elsewhere on the board
PHASE_B: D202.1 (K), R205.2, R206.2, R208.1; also elsewhere on the board
PHASE_C: D302.1 (K), R305.2, R306.2, R308.1; also elsewhere on the board
QSPI_SCLK: U7.56 (QSPI_SCLK), U8.6 (CLK)
QSPI_SD0: U7.57 (QSPI_SD0), U8.5 (DI/IO_{0})
QSPI_SD1: U7.59 (QSPI_SD1), U8.2 (DO/IO_{1})
QSPI_SD2: U7.58 (QSPI_SD2), U8.3 (~WP/IO_{2})
QSPI_SD3: U7.55 (QSPI_SD3), U8.7 (~HOLD/~RESET/IO_{3})
QSPI_SS: R701.1, U7.60 (QSPI_SS), U8.1 (~CS)
RS485_IN_RX: U7.3 (GPIO1); also elsewhere on the board
RS485_IN_TX: U7.2 (GPIO0); also elsewhere on the board
RS485_OUT_RX: U7.19 (GPIO15); also elsewhere on the board
RS485_OUT_TX: U7.18 (GPIO14); also elsewhere on the board
RUN: C717.1, R704.1, U7.26 (RUN); also elsewhere on the board
SNSN_A: C108.2, R108.2, U4.1 (-)
SNSN_B: C208.2, R208.2, U5.1 (-)
SNSN_C: C308.2, R308.2, U6.1 (-)
SNSP_A: C108.1, R107.1, U4.8 (+)
SNSP_B: C208.1, R207.1, U5.8 (+)
SNSP_C: C308.1, R307.1, U6.8 (+)
SNUB_A: C109.2, R113.1
SNUB_B: C209.2, R213.1
SNUB_C: C309.2, R313.1
SWCLK: U7.24 (SWCLK); also elsewhere on the board
SWDIO: U7.25 (SWD); also elsewhere on the board
SW_A: C105.2, Q1.1 (S), Q1.2 (S), Q1.3 (S), Q2.5 (D), R105.1, R106.1, R107.2, R109.2, R113.2, U1.6 (VS)
SW_B: C205.2, Q3.1 (S), Q3.2 (S), Q3.3 (S), Q4.5 (D), R205.1, R206.1, R207.2, R209.2, R213.2, U2.6 (VS)
SW_C: C305.2, Q5.1 (S), Q5.2 (S), Q5.3 (S), Q6.5 (D), R305.1, R306.1, R307.2, R309.2, R313.2, U3.6 (VS)
USB_DM: R708.1; also elsewhere on the board
USB_DM_C: R708.2, U7.51 (USB_DM)
USB_DP: R707.1; also elsewhere on the board
USB_DP_C: R707.2, U7.52 (USB_DP)
USB_VBUS_DET: U7.37 (GPIO25); also elsewhere on the board
VBUS: C101.1, C102.1, C103.1, C104.1, C201.1, C202.1, C203.1, C204.1, C301.1, C302.1, C303.1, C304.1, Q1.5 (D), Q3.5 (D), Q5.5 (D); also elsewhere on the board
VBUS_SENSE: U7.42 (GPIO28_ADC2); also elsewhere on the board
VB_A: C105.1, D101.1 (K), U1.8 (VB)
VB_B: C205.1, D201.1 (K), U2.8 (VB)
VB_C: C305.1, D301.1 (K), U3.8 (VB)
VREG_AVDD: C718.1, R706.2, U7.46 (VREG_AVDD)
VREG_LX: L701.2, U7.48 (VREG_LX)
XIN: C709.1, U7.21 (XIN), Y1.1
XOUT: R702.1, U7.22 (XOUT)
XTAL2: C710.1, R702.2, Y1.3

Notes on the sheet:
Phase A
Phase B
Phase C
RP2350A
QSPI flash
3V3 LDO
Decoupling
Notes: the power bridge
Each phase is an EG2103 half-bridge driver on a pair of BSC030N08NS5: bootstrap diode and capacitor (D101, C105 on phase A), 2R2 gate resistors, 10k gate-source pull-downs. HIN and LIN are held low (R111, R112): with both low the EG2103 turns the low side on, so a CPU in reset brakes the motor. Inl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
Notes: the CPU
RP2350A as Raspberry Pi's minimal design (RP-006440): the core supply is the chip's own switching regulator, VREG_LX through L701 to +1V1, which VREG_FB senses and DVDD takes. VREG_AVDD is +3V3 through R706 and C718. One 100n at each IOVDD pin (C701-C706); C714 4u7 at VREG_VIN. ADC_AVDD is +3V3 fil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

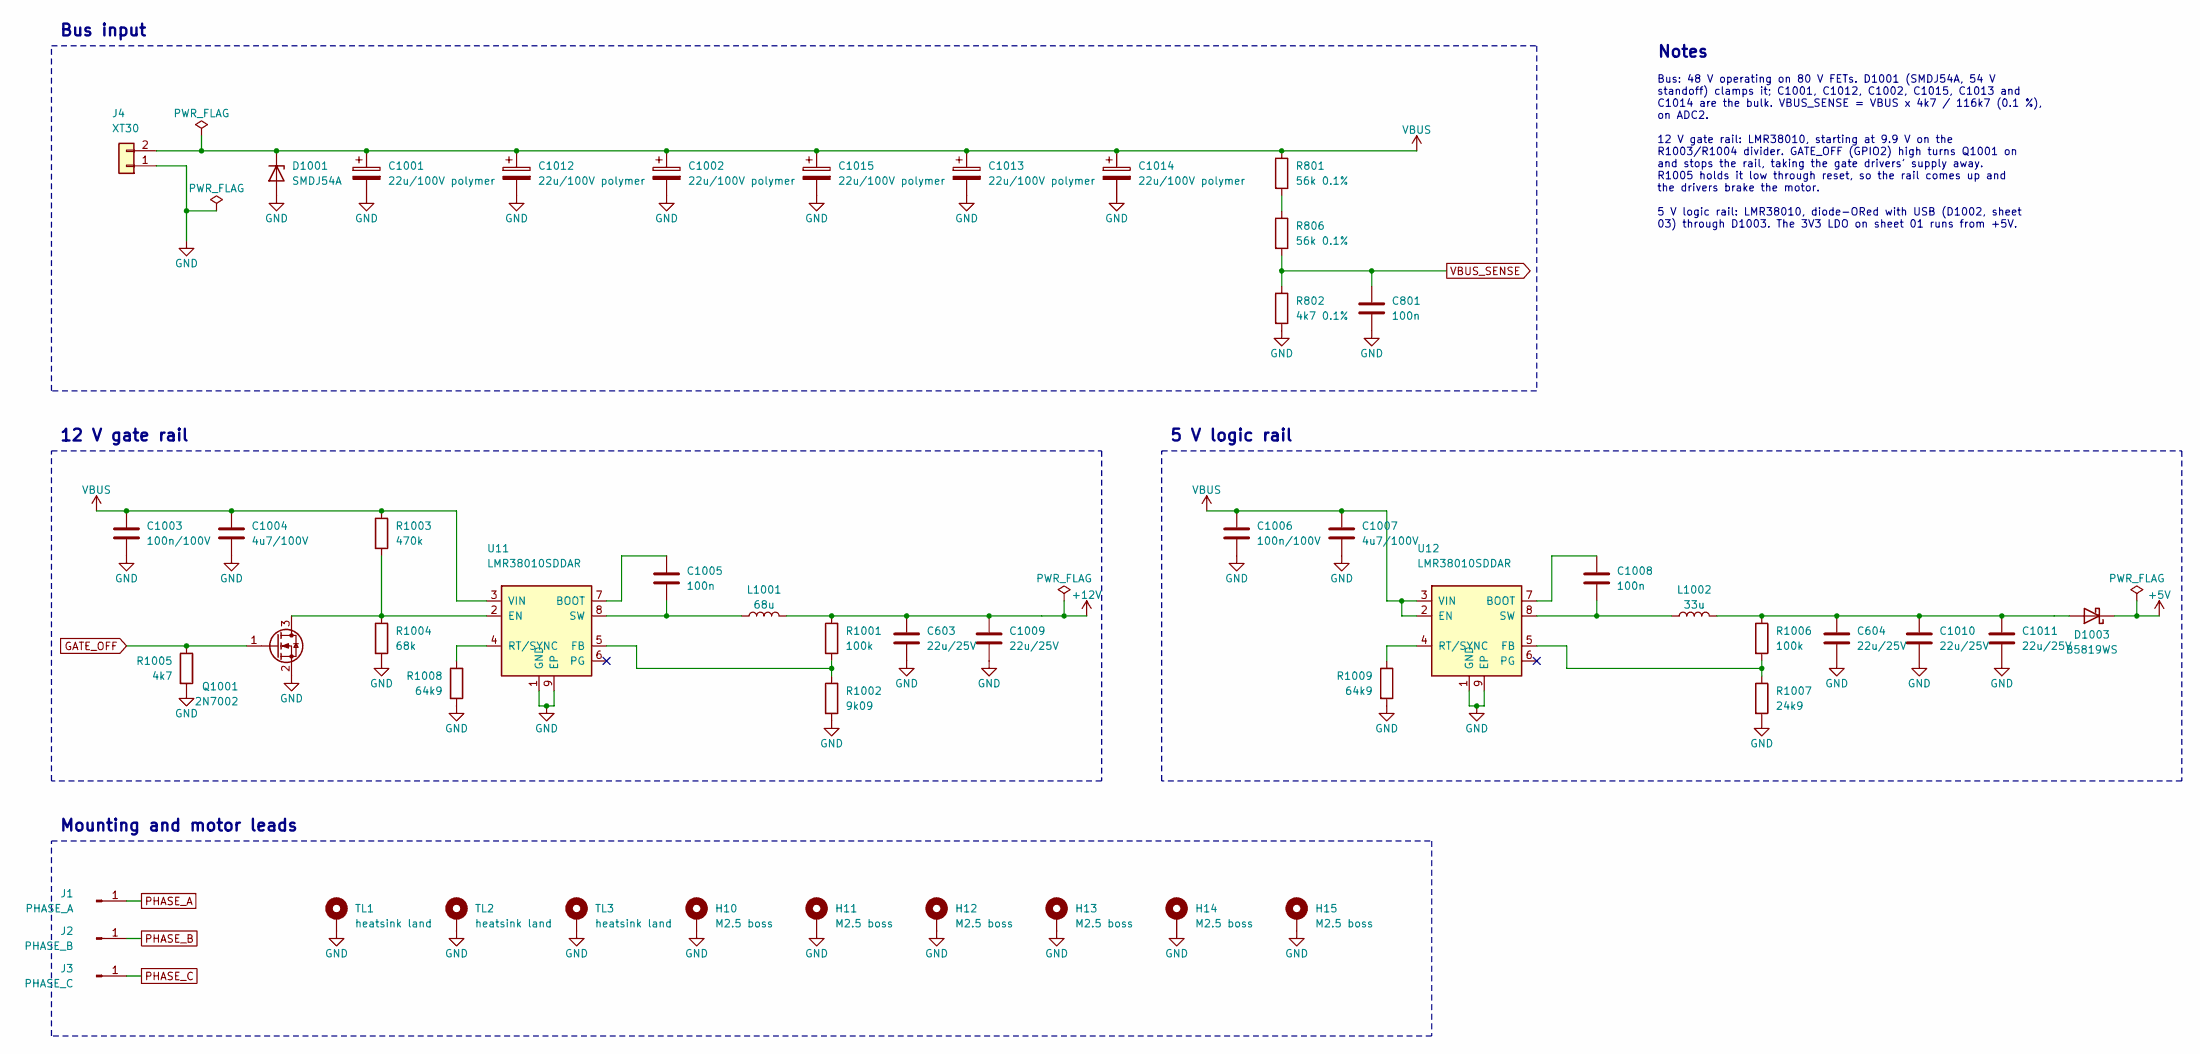
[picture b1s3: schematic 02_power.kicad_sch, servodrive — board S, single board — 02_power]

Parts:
C603: 22u/25V; C_1206_3216Metric
C604, C1010, C1011: 22u/25V; C_0805_2012Metric
C801: 100n; C_0603_1608Metric
C1001, C1002, C1012, C1013, C1014, C1015: 22u/100V polymer; CP_Radial_D6.3mm_P2.50mm
C1003, C1006: 100n/100V; C_0805_2012Metric
C1004, C1007: 4u7/100V; C_1206_3216Metric
C1005, C1008: 100n; C_0402_1005Metric
C1009: 22u/25V; C_1210_3225Metric
D1001: SMDJ54A; D_SMC
D1003: B5819WS; D_SOD-323
H10, H11, H12, H13, H14, H15: M2.5 boss; ThermalBoss_M2.5
J1: PHASE_A; PhasePad_Arc
J2: PHASE_B; PhasePad_Arc
J3: PHASE_C; PhasePad_Arc
J4: XT30; AMASS_XT30PW-M_1x02_P2.50mm_Horizontal
L1001: 68u; L_Sunlord_SWPA4030S
L1002: 33u; L_Sunlord_SWPA4030S
Q1001: 2N7002; SOT-23
R801, R806: 56k 0.1%; R_0603_1608Metric
R802: 4k7 0.1%; R_0603_1608Metric
R1001, R1006: 100k; R_0402_1005Metric
R1002: 9k09; R_0402_1005Metric
R1003: 470k; R_0402_1005Metric
R1004: 68k; R_0402_1005Metric
R1005: 4k7; R_0402_1005Metric
R1007: 24k9; R_0402_1005Metric
R1008, R1009: 64k9; R_0402_1005Metric
TL1, TL2, TL3: heatsink land; ThermalLand_Phase
U11, U12: LMR38010SDDAR; TI_SO-PowerPAD-8

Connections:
+5V: D1003.1 (K); also elsewhere on the board
+5V_BUCK: C604.1, C1010.1, C1011.1, D1003.2 (A), L1002.2, R1006.1
+12V: C603.1, C1009.1, L1001.2, R1001.1; also elsewhere on the board
BOOT_5V: C1008.1, U12.7 (BOOT)
BOOT_12V: C1005.1, U11.7 (BOOT)
EN_12V: Q1001.3 (D), R1003.2, R1004.1, U11.2 (EN)
FB_5V: R1006.2, R1007.1, U12.5 (FB)
FB_12V: R1001.2, R1002.1, U11.5 (FB)
GATE_OFF: Q1001.1 (G), R1005.1; also elsewhere on the board
GND: C603.2, C604.2, C801.2, C1001.2, C1002.2, C1003.2, C1004.2, C1006.2, C1007.2, C1009.2, C1010.2, C1011.2, C1012.2, C1013.2, C1014.2, C1015.2, D1001.2 (A), H10.1, H11.1, H12.1, H13.1, H14.1, H15.1, J4.1, Q1001.2 (S), R802.2, R1002.2, R1004.2, R1005.2, R1007.2, R1008.2, R1009.2, TL1.1, TL2.1, TL3.1, U11.1 (GND), U11.9 (EP), U12.1 (GND), U12.9 (EP); also elsewhere on the board
PHASE_A: J1.1; also elsewhere on the board
PHASE_B: J2.1; also elsewhere on the board
PHASE_C: J3.1; also elsewhere on the board
RT_5V: R1009.1, U12.4 (RT/SYNC)
RT_12V: R1008.1, U11.4 (RT/SYNC)
SW_5V: C1008.2, L1002.1, U12.8 (SW)
SW_12V: C1005.2, L1001.1, U11.8 (SW)
VBUS: C1001.1, C1002.1, C1003.1, C1004.1, C1006.1, C1007.1, C1012.1, C1013.1, C1014.1, C1015.1, D1001.1 (K), J4.2, R801.1, R1003.1, U11.3 (VIN), U12.2 (EN), U12.3 (VIN); also elsewhere on the board
VBUS_SENSE: C801.1, R802.1, R806.2; also elsewhere on the board
VDIV_MID: R801.2, R806.1

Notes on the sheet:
Bus input
12 V gate rail
5 V logic rail
Mounting and motor leads
Notes
Bus: 48 V operating on 80 V FETs. D1001 (SMDJ54A, 54 V standoff) clamps it; C1001, C1012, C1002, C1015, C1013 and C1014 are the bulk. VBUS_SENSE = VBUS x 4k7 / 116k7 (0.1 %), on ADC2. 12 V gate rail: LMR38010, starting at 9.9 V on the R1003/R1004 divider. GATE_OFF (GPIO2) high turns Q1001 on and st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

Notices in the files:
README.md:
Licence:
CERN-OHL-P, like its parent. Design by Sequoia Hope Alexander.
hardware/single_board/01_bridge_cpu.kicad_sch:
CERN-OHL-P
